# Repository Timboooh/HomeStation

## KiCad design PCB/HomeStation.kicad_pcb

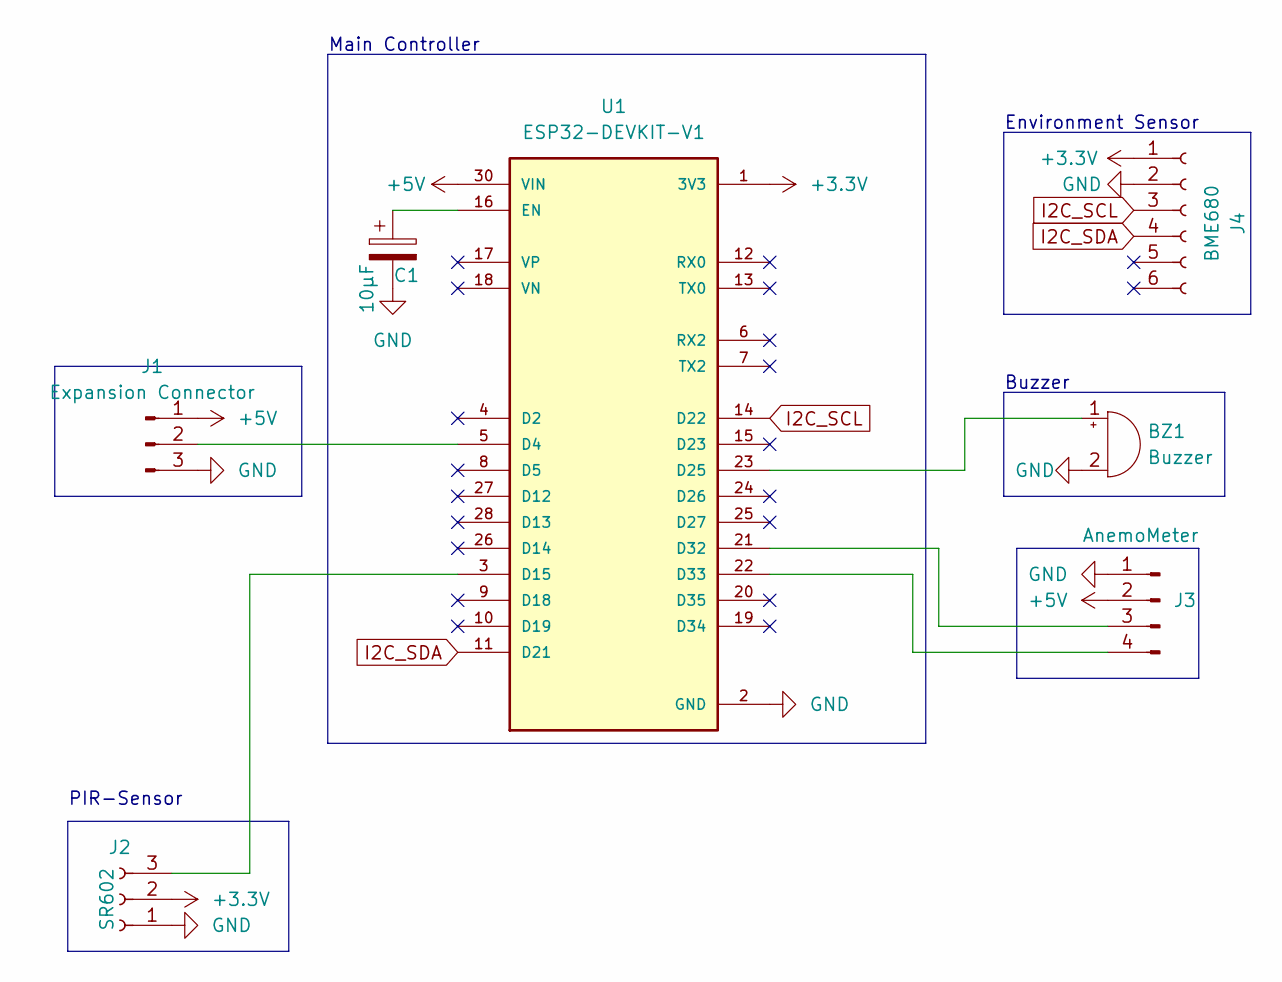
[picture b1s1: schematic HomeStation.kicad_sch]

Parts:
BZ1: Buzzer; Buzzer_12x9.5RM7.6
C1: 10µF; C_Radial_D5.0mm_H7.0mm_P2.00mm
J1: Expansion Connector; PinHeader_1x03_P2.54mm_Vertical
J2: SR602; PinSocket_1x03_P2.54mm_Vertical
J3: AnemoMeter; PinHeader_1x04_P2.54mm_Vertical
J4: BME680; PinSocket_1x06_P2.54mm_Vertical
U1: ESP32-DEVKIT-V1; MODULE_ESP32_DEVKIT_V1; PARTREV N/A

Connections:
+3V3: J2.2, J4.1, U1.1 (3V3)
+5V: J1.1, J3.2, U1.30 (VIN)
GND: BZ1.2 (+), C1.2, J1.3, J2.1, J3.1, J4.2, U1.2 (GND)
I2C_SCL: J4.3, U1.14 (D22)
I2C_SDA: J4.4, U1.11 (D21)
unnamed: BZ1.1 (-), U1.23 (D25)
unnamed: C1.1, U1.16 (EN)
unnamed: J1.2, U1.5 (D4)
unnamed: J2.3, U1.3 (D15)
unnamed: J3.3, U1.21 (D32)
unnamed: J3.4, U1.22 (D33)

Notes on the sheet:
PIR-Sensor
Buzzer
Main Controller
Environment Sensor

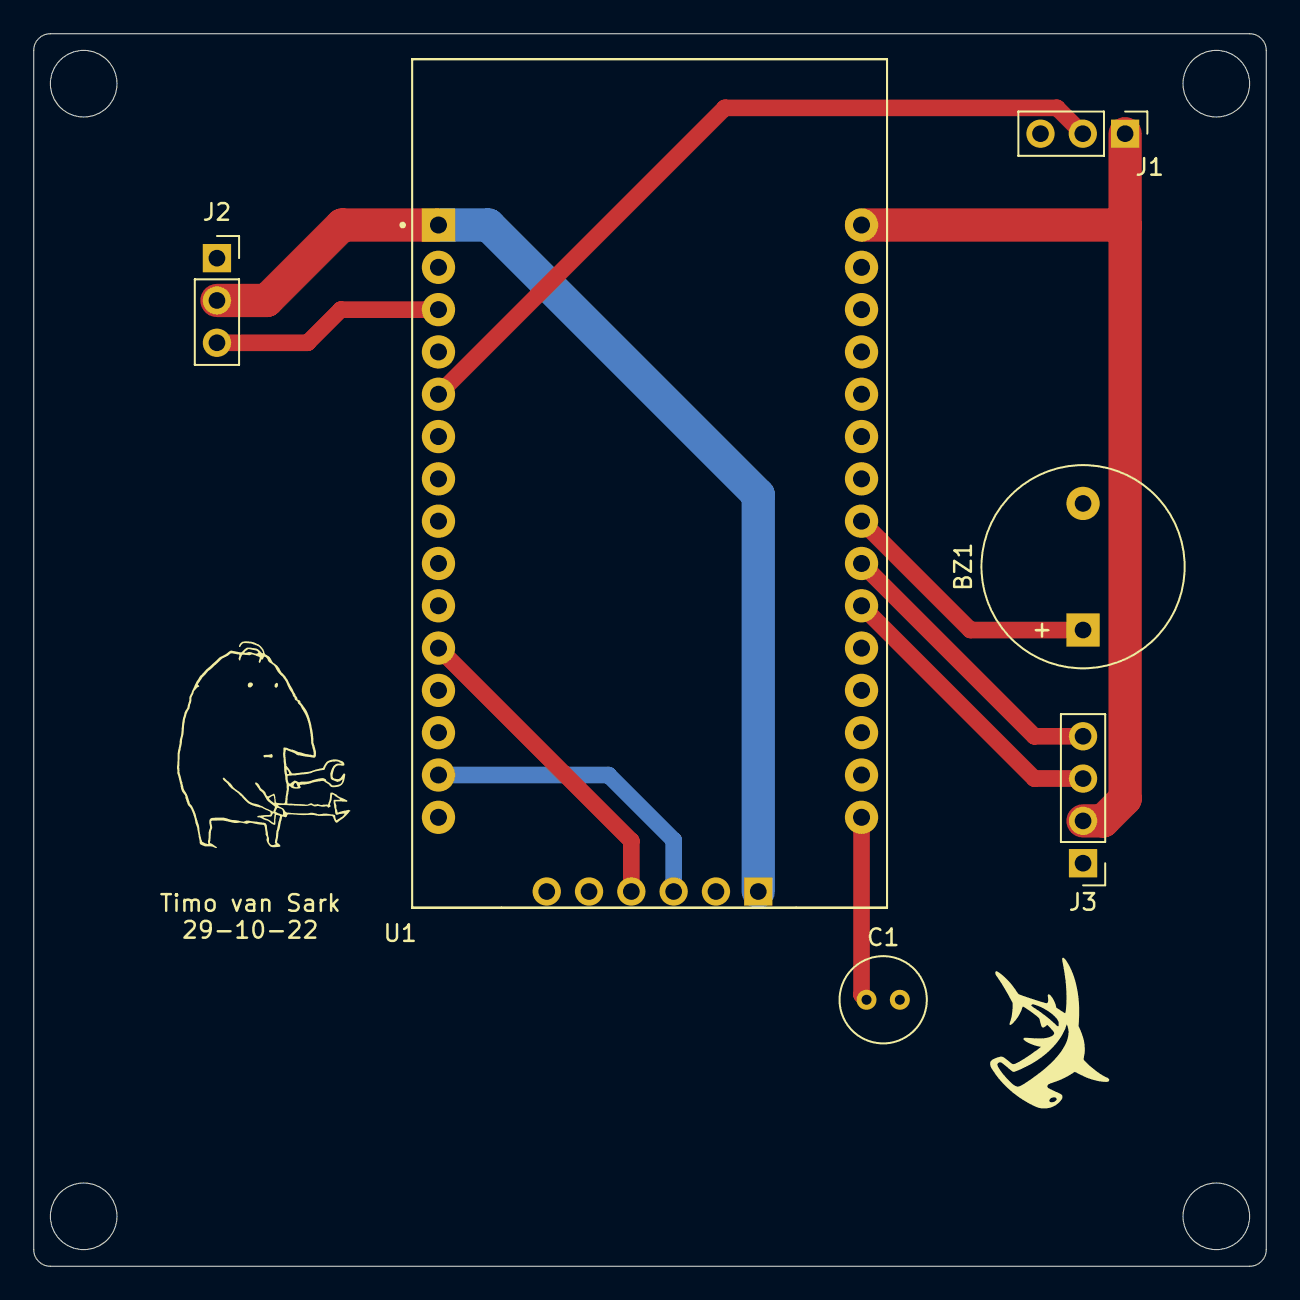
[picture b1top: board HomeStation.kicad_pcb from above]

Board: 2 copper layers, 74.0 x 74.0 mm, 7 parts (1 on the bottom side), 11 nets.

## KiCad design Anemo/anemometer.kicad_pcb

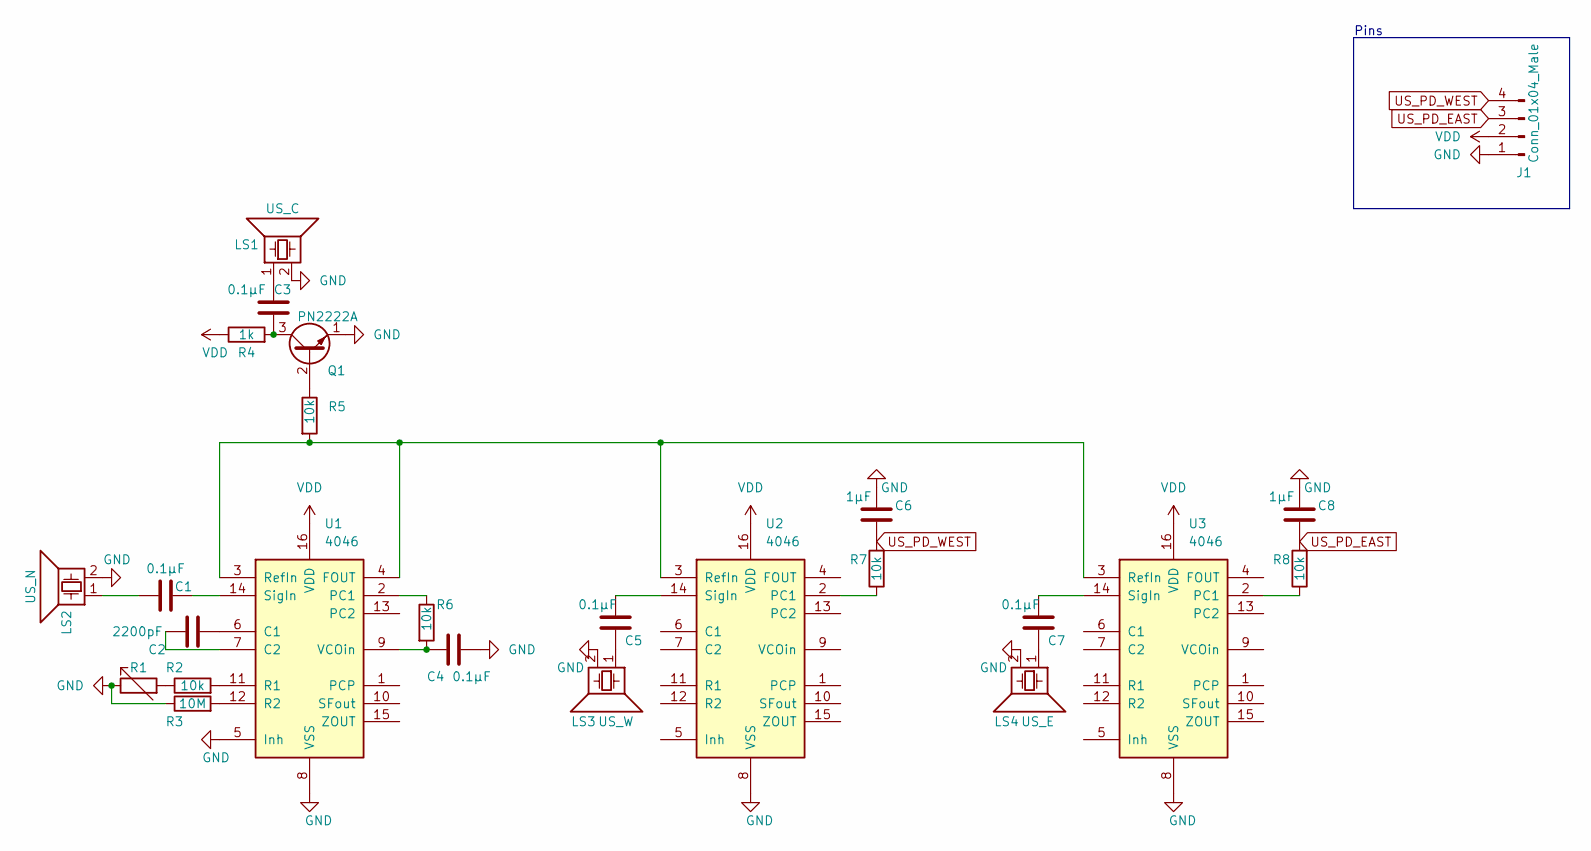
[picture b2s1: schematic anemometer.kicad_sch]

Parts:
C1, C3, C4, C5, C7: 0.1µF; C_Disc_D5.0mm_W2.5mm_P5.00mm
C2: 2200pF; C_Disc_D5.0mm_W2.5mm_P5.00mm
C6, C8: 1µF; C_Disc_D5.0mm_W2.5mm_P5.00mm
J1: Conn_01x04_Male; PinHeader_1x04_P2.54mm_Vertical
LS1: US_C; Buzzer_D14mm_H7mm_P10mm
LS2: US_N; Buzzer_D14mm_H7mm_P10mm
LS3: US_W; Buzzer_D14mm_H7mm_P10mm
LS4: US_E; Buzzer_D14mm_H7mm_P10mm
Q1: PN2222A; TO-92_Inline
R1: (no value)
R2, R5, R6, R7, R8: 10k; R_0805_2012Metric_Pad1.20x1.40mm_HandSolder
R3: 10M; R_0805_2012Metric_Pad1.20x1.40mm_HandSolder
R4: 1k; R_0805_2012Metric_Pad1.20x1.40mm_HandSolder
U1, U2, U3: 4046; DIP-16_W7.62mm_Socket_LongPads

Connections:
GND: C4.1, C6.2, C8.2, J1.1, LS1.2, LS2.2, LS3.2, LS4.2, Q1.1 (E), R1.1, R3.1, U1.5 (Inh), U1.8 (VSS), U2.8 (VSS), U3.8 (VSS)
unnamed: C1.1, LS2.1
unnamed: C1.2, U1.14 (SigIn)
unnamed: C2.1, U1.6 (C1)
unnamed: C2.2, U1.7 (C2)
unnamed: C3.1, LS1.1
unnamed: C3.2, Q1.3 (C), R4.2
unnamed: C4.2, R6.2, U1.9 (VCOin)
unnamed: C5.1, LS3.1
unnamed: C5.2, U2.14 (SigIn)
unnamed: C7.1, LS4.1
unnamed: C7.2, U3.14 (SigIn)
unnamed: Q1.2 (B), R5.1
unnamed: R1.2, R2.1
unnamed: R2.2, U1.11 (R1)
unnamed: R3.2, U1.12 (R2)
unnamed: R5.2, U1.3 (RefIn), U1.4 (FOUT), U2.3 (RefIn), U3.3 (RefIn)
unnamed: R6.1, U1.2 (PC1)
unnamed: R7.1, U2.2 (PC1)
unnamed: R8.1, U3.2 (PC1)
US_PD_EAST: C8.1, J1.3, R8.2
US_PD_WEST: C6.1, J1.4, R7.2
VDD: J1.2, R4.1, U1.16 (VDD), U2.16 (VDD), U3.16 (VDD)

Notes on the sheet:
Pins

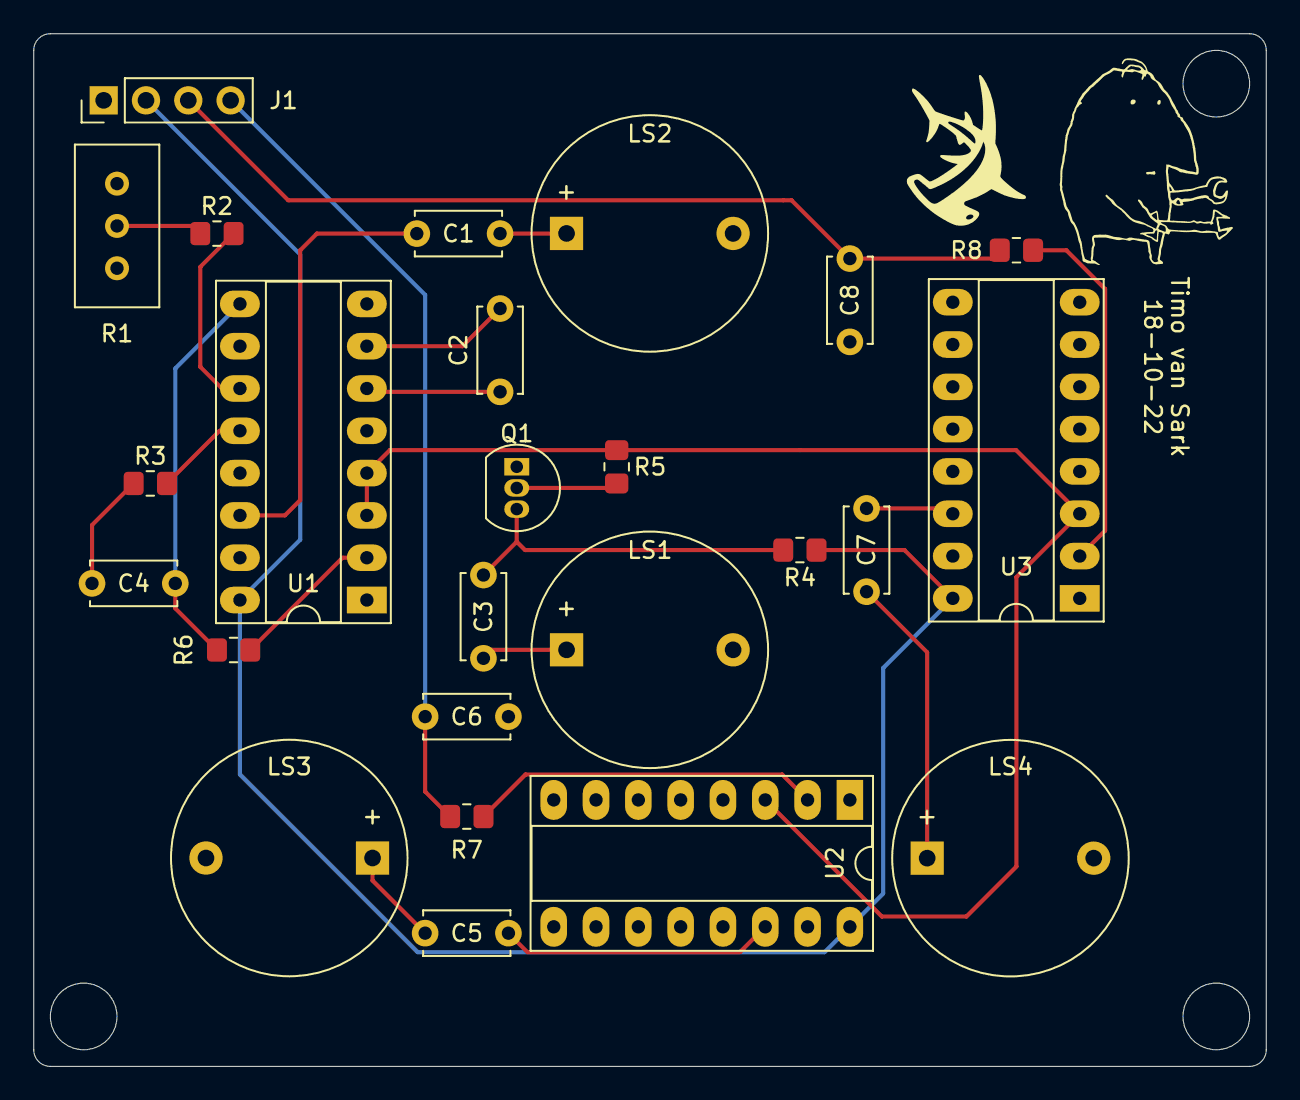
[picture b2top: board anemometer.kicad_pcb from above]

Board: 2 copper layers, 74.0 x 62.0 mm, 25 parts (0 on the bottom side), 23 nets.

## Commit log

2022-09-06 Create .gitignore for Controller Project
2022-09-06 Create Empty Project
2022-09-06 Add PubSub dependency
2022-09-07 Test MQTT connectivity
2022-09-14 Basic functionality
2022-09-19 Move sensors into seperate modules & fix .gitignore
2022-09-19 Add code-workspace
2022-09-19 Create Simple SR602 driver
2022-09-21 temp
2022-09-29 Add empty KiCad Project
2022-09-29 Add 1.0 Schematic
2022-10-03 Fix MQTT crashing
2022-10-12 Add location data
2022-10-18 WIP - PCB
2022-10-18 Anemo PCB
2022-11-08 yeye
2022-11-08 old case
2022-11-08 Bakje 2.0
